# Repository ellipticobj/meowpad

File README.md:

# meowpad
this is my submission for hackclub's hackpadv2 ysws.

i used kicad for the pcb, bricscad for the case, and kmk for the firmware

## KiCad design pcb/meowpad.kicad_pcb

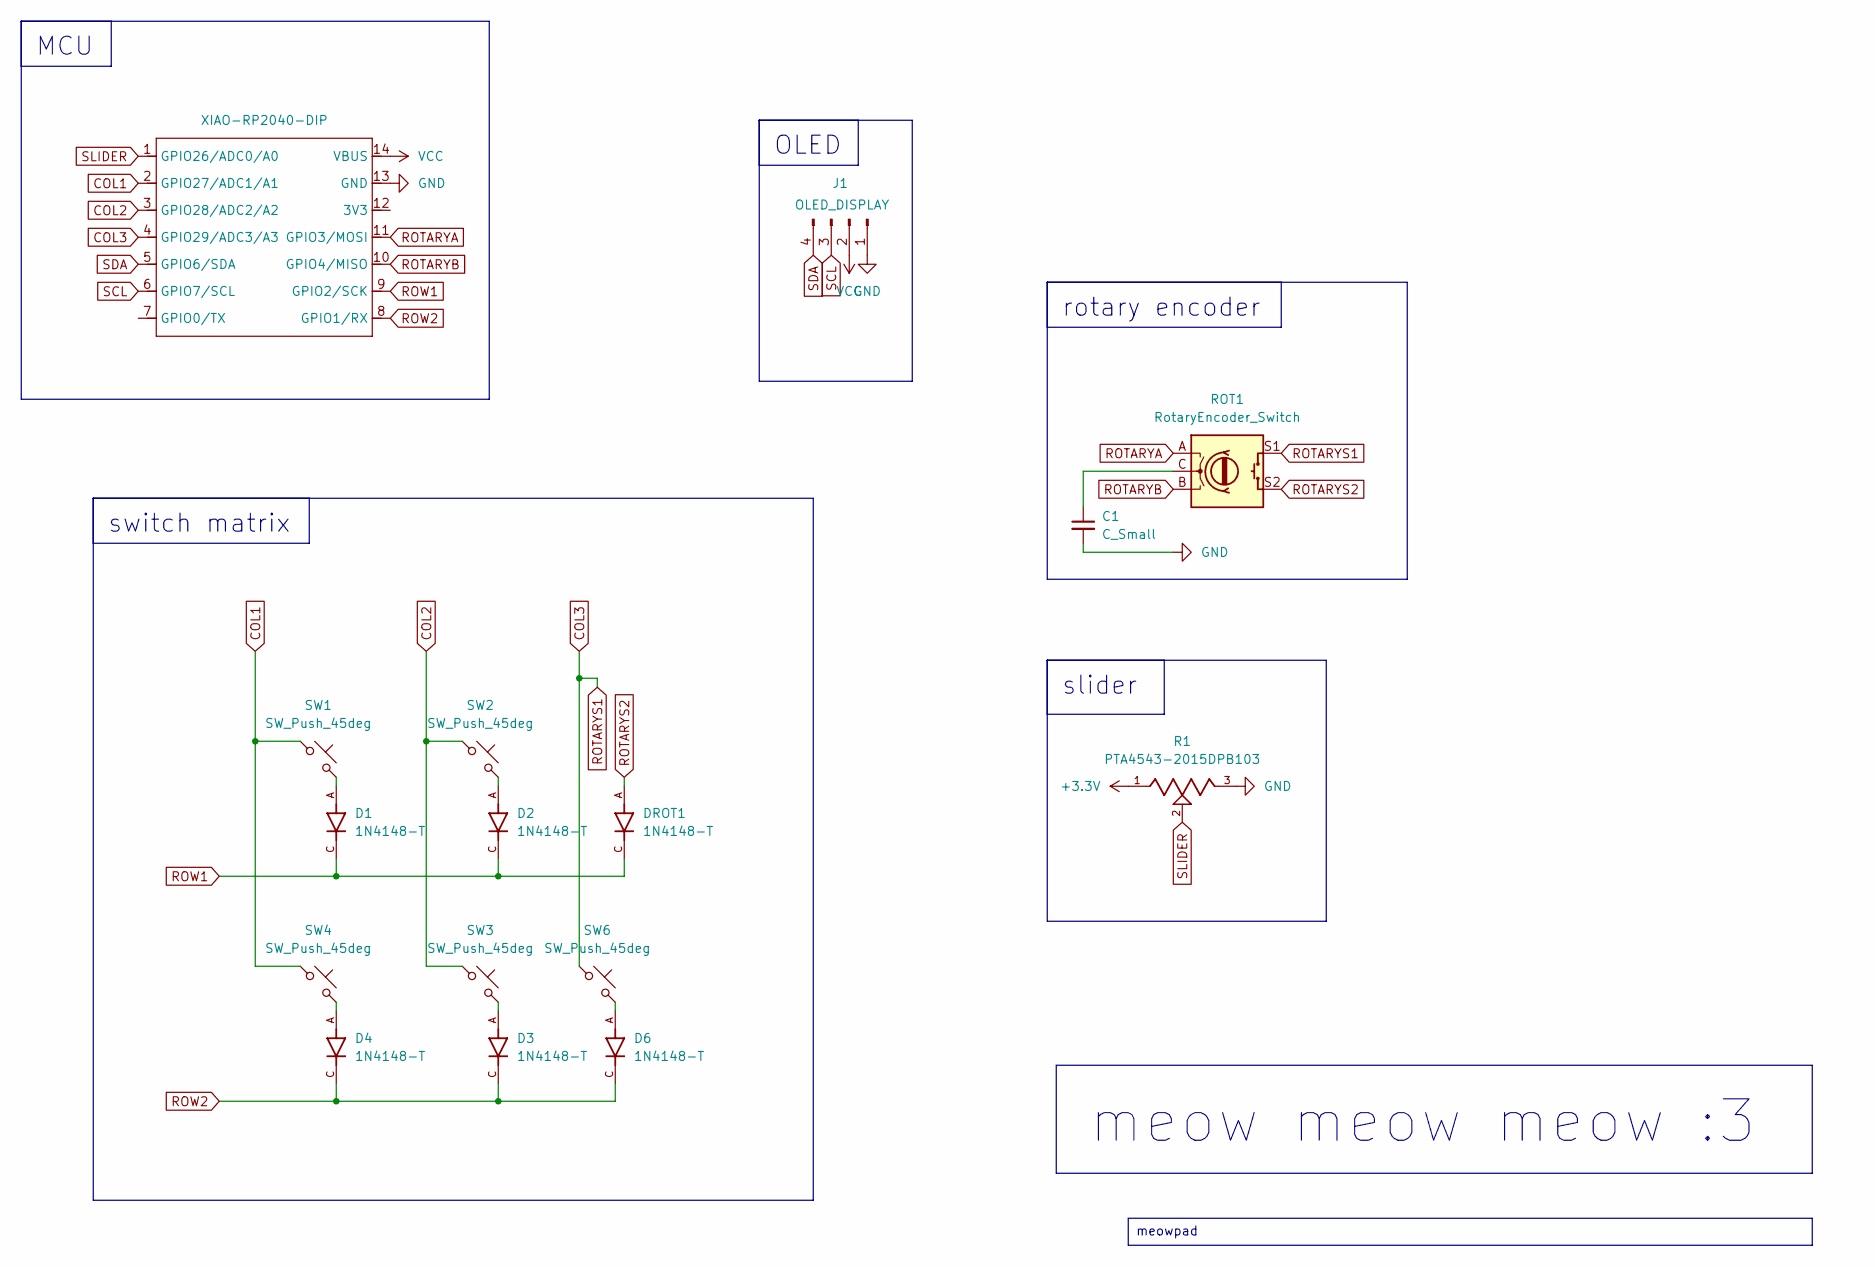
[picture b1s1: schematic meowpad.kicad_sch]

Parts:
C1: C_Small; CP_Radial_D5.0mm_P2.50mm
D1, D2, D3, D4, D6: 1N4148-T; DIOAD820W60L400D200; PARTREV 9-3
DROT1: 1N4148-T; DIOAD820W60L400D200; PARTREV 9-3
J1: OLED_DISPLAY; SSD1306-0.91-OLED-4pin-128x32
R1: PTA4543-2015DPB103; TRIM_PTA4543-2015DPB103; PARTREV 04/21
ROT1: RotaryEncoder_Switch; RotaryEncoder_Alps_EC11E-Switch_Vertical_H20mm_MountingHoles
SW1, SW2, SW3, SW4, SW6: SW_Push_45deg; SW_Cherry_MX_1.00u_PCB
U2: XIAO-RP2040-DIP; XIAO-RA4M1-SMD

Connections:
+3.3V: R1.1
COL1: SW1.1, SW4.1, U2.2 (GPIO27/ADC1/A1)
COL2: SW2.1, SW3.1, U2.3 (GPIO28/ADC2/A2)
COL3: ROT1.S1, SW6.1, U2.4 (GPIO29/ADC3/A3)
GND: C1.2, J1.1, R1.3, U2.13 (GND)
unnamed: C1.1, ROT1.C
unnamed: D1.A, SW1.2
unnamed: D2.A, SW2.2
unnamed: D3.A, SW3.2
unnamed: D4.A, SW4.2
unnamed: D6.A, SW6.2
ROTARYA: ROT1.A, U2.11 (GPIO3/MOSI)
ROTARYB: ROT1.B, U2.10 (GPIO4/MISO)
ROTARYS2: DROT1.A, ROT1.S2
ROW1: D1.C, D2.C, DROT1.C, U2.9 (GPIO2/SCK)
ROW2: D3.C, D4.C, D6.C, U2.8 (GPIO1/RX)
SCL: J1.3, U2.6 (GPIO7/SCL)
SDA: J1.4, U2.5 (GPIO6/SDA)
SLIDER: R1.2, U2.1 (GPIO26/ADC0/A0)
VCC: J1.2, U2.14 (VBUS)

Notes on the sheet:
meowpad
rotary encoder
meow meow meow :3
switch matrix
MCU
slider
OLED

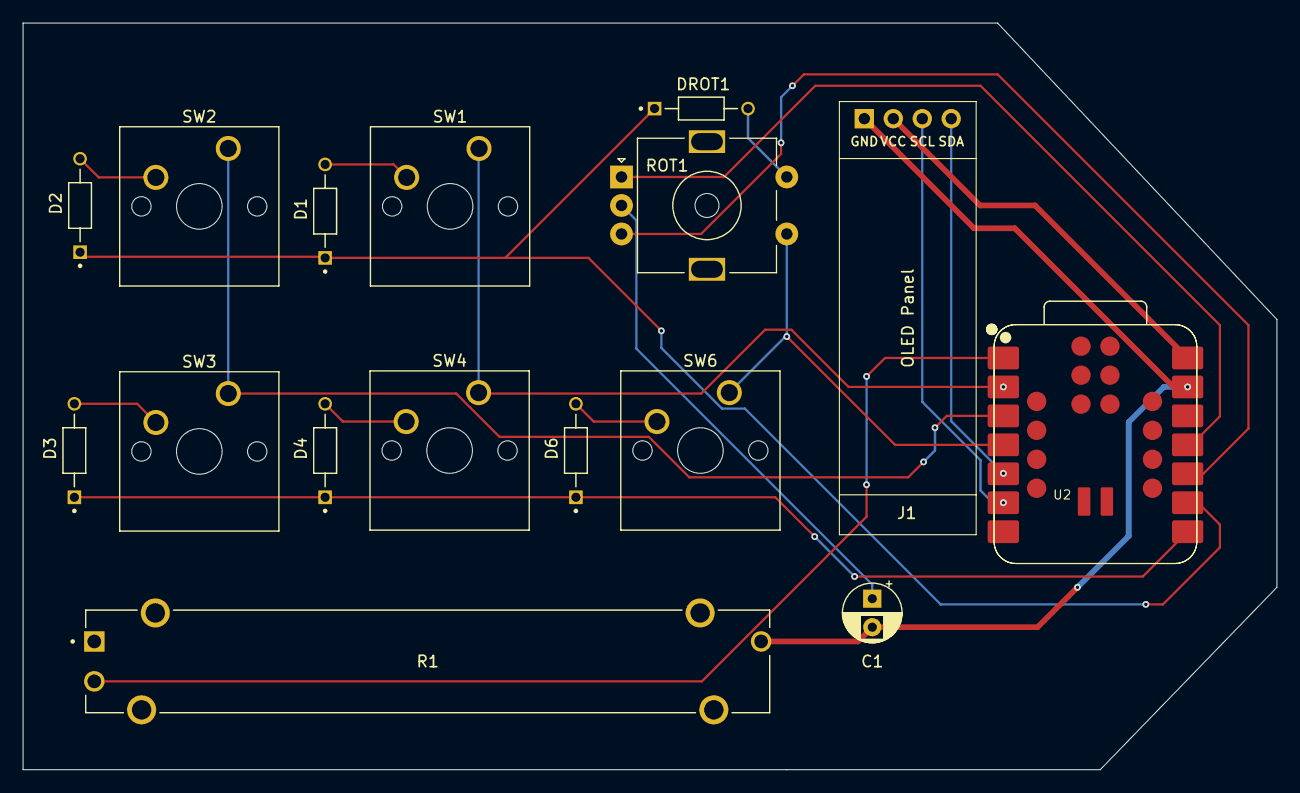
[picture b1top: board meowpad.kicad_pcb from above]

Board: 2 copper layers, 110.0 x 65.5 mm, 16 parts (0 on the bottom side), 19 nets.

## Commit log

2025-02-05 added pcb files
2025-02-05 added cad
2025-02-06 started on this thing
2025-02-06 key matrix
2025-02-06 rotary encoder
2025-02-06 keymaps + rotary encoder layer switcher
2025-02-06 oled displays ram and cpu now
2025-02-06 bill of materials
2025-02-06 cad updates
2025-02-06 production folder
2025-02-06 finalizing submission
